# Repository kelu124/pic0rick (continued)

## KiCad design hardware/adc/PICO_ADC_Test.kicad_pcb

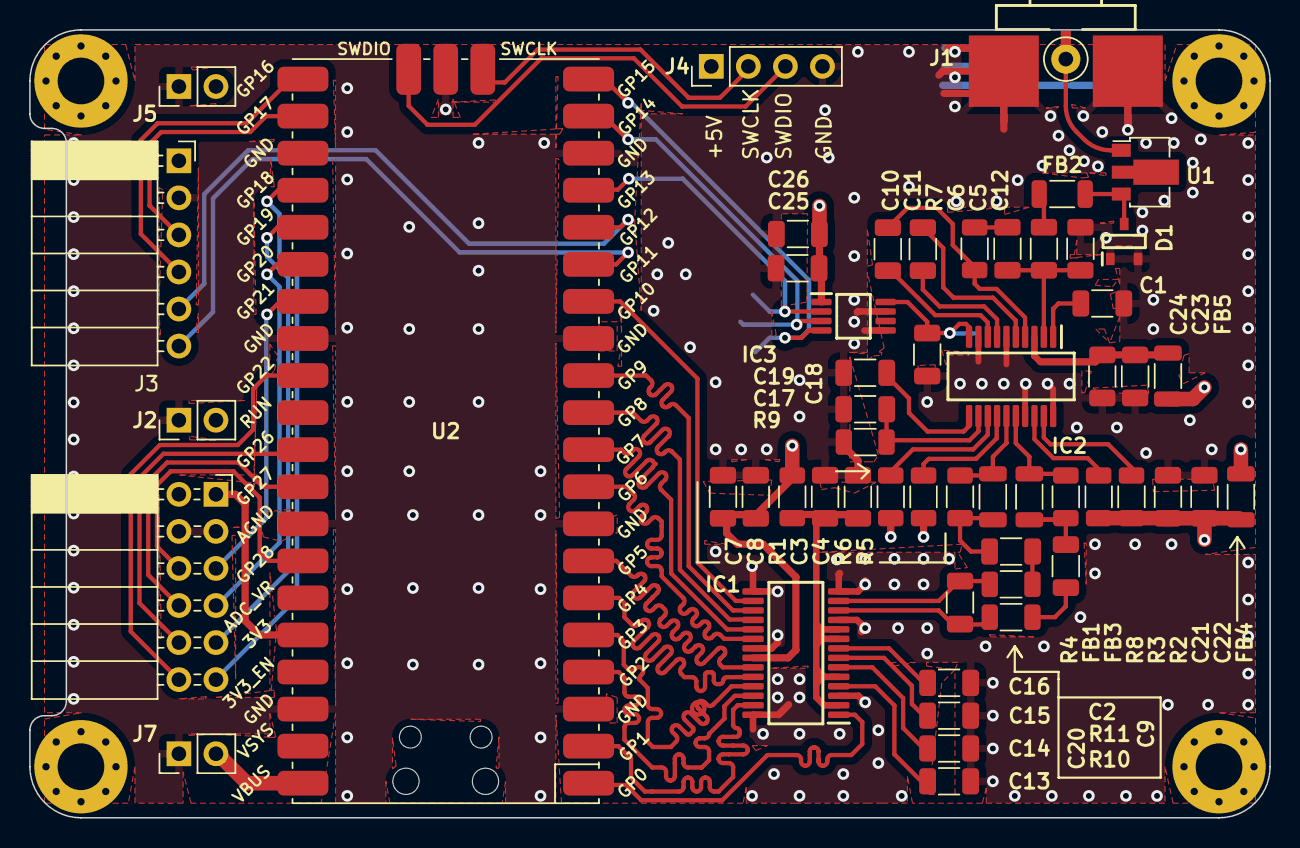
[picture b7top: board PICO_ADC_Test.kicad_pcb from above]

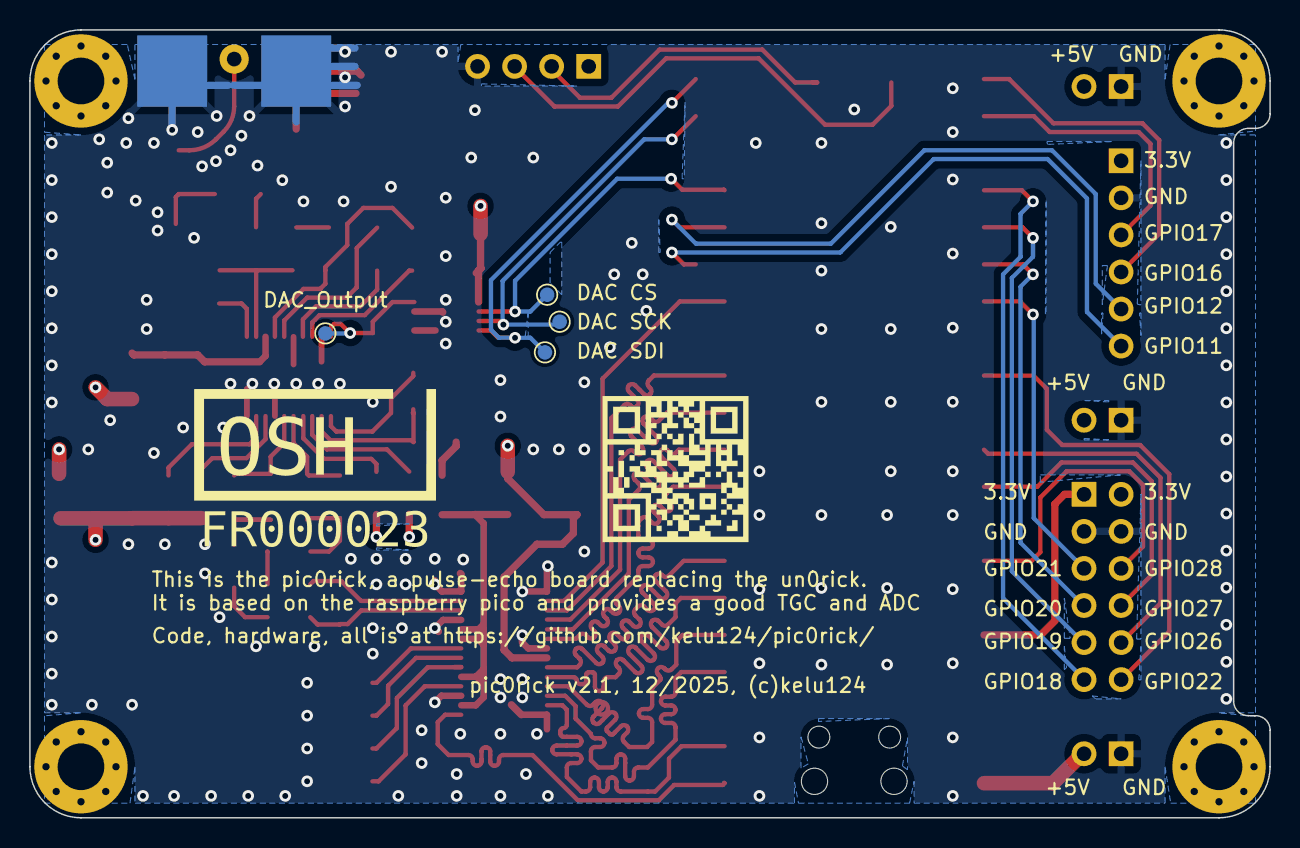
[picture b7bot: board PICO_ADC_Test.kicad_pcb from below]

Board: 4 copper layers, 85.0 x 54.0 mm, 59 parts (4 on the bottom side), 63 nets.

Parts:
C1, C2, C4, C5, C8, C9, C10, C11, C13, C14, C15, C16, C17, C19, C22, C24, C26: 100nF; C_1206_3216Metric
C3, C7: 4.7uF; C_1206_3216Metric
C6: 18nF; C_1206_3216Metric
C12: 22pF; C_1206_3216Metric
C18, C21, C23: 1nF; C_1206_3216Metric
C20: 50pF; C_1206_3216Metric
C25: 10uF; C_1206_3216Metric
D1: BAV99-7-F; SOT95P240X120-3N
FB1, FB2, FB3, FB4, FB5: ILHB1206ER750V; L_1206_3216Metric
IC1: ADC10065CIMT_NOPB; SOP65P640X120-28N
IC2: AD8331ARQZ; SOP64P600X175-20N
IC3: MCP4812-E_MS; MCP4812-EMS
J1: AMPHENOL_132357-11
J2, J5, J7: SSQ-101-02-L-Q-RA; PinHeader_1x02_P2.54mm_Vertical
J3: 61300611121; PinSocket_1x06_P2.54mm_Horizontal
J4: 61300411121; PinHeader_1x04_P2.54mm_Vertical
J6: 90122-0126; PinSocket_2x06_P2.54mm_Horizontal
R1, R10, R11: 18R; R_1206_3216Metric
R2, R3, R5, R6: 10K; R_1206_3216Metric
R4, R8: 100R; R_1206_3216Metric
R7: 280R; R_1206_3216Metric
R9: 12K; R_1206_3216Metric
TP1, TP2, TP3, TP4: TestPoint; TestPoint_Pad_D1.0mm
U1: MD0100N8-G; SOT-89-3
U2: Pico; RPi_Pico_SMD

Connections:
5VLNA: C23.1, C24.1, FB5.2, IC2.3 (VPSL)
5VVGA: C21.1, C22.1, FB4.1, R2.1, R3.1, R5.1, R6.1
+3.3V: C7.1, C8.1, C25.1, C26.1, IC1.22 (VDDIO), IC3.1 (VDD), J3.1, J6.1, J6.2, R1.1, U2.36 (3V3)
+5V: FB4.2, FB5.1, J2.2, J4.1, J5.2, J7.2, U2.40 (VBUS)
ADC_CLK: IC1.1 (CLK), U2.1 (GPIO0)
CS: IC3.2 (~CS), TP1.1, U2.17 (GPIO13)
D0: IC1.27 (D0), U2.2 (GPIO1)
D1: IC1.26 (D1), U2.4 (GPIO2)
D2: IC1.25 (D2), U2.5 (GPIO3)
D3: IC1.24 (D3), U2.6 (GPIO4)
D4: IC1.23 (D4), U2.7 (GPIO5)
D5: IC1.20 (D5), U2.9 (GPIO6)
D6: IC1.19 (D6), U2.10 (GPIO7)
D7: IC1.18 (D7), U2.11 (GPIO8)
D8: IC1.17 (D8), U2.12 (GPIO9)
D9: IC1.16 (D9), U2.14 (GPIO10)
DAC_G: C18.1, IC2.10 (GAIN), IC3.8 (VOUTA), TP4.1
GND: C1.1, C3.2, C4.2, C7.2, C8.2, C12.2, C13.2, C14.2, C15.2, C16.2, C17.2, C18.2, C19.2, C21.2, C22.2, C23.2, C24.2, C25.2, C26.2, D1.1, D1.2, IC1.3 (VSSA_1), IC1.11 (VSSA_2), IC1.14 (VSSA_3), IC1.15 (DF), IC1.21 (VSSIO), IC1.28 (STBY), IC2.6 (COML), IC2.9 (MODE), IC2.17 (COMM_1), IC2.20 (COMM_2), IC3.5 (~LDAC), IC3.7 (VSS), J1.2, J2.1, J3.2, J4.4, J5.1, J6.3, J6.4, J7.1, R9.2, U2.3 (GND), U2.8 (GND), U2.13 (GND), U2.18 (GND), U2.23 (GND), U2.28 (GND), U2.33 (AGND), U2.38 (GND), U2.42 (GND)
GPIO11: J3.6, U2.15 (GPIO11)
GPIO12: J3.5, U2.16 (GPIO12)
GPIO16: J3.4, U2.21 (GPIO16)
GPIO17: J3.3, U2.22 (GPIO17)
GPIO18: J6.11, U2.24 (GPIO18)
GPIO19: J6.9, U2.25 (GPIO19)
GPIO20: J6.7, U2.26 (GPIO20)
GPIO21: J6.5, U2.27 (GPIO21)
GPIO22: J6.12, U2.29 (GPIO22)
GPIO26: J6.10, U2.31 (GPIO26_ADC0)
GPIO27: J6.8, U2.32 (GPIO27_ADC1)
GPIO28: J6.6, U2.34 (GPIO28_ADC2)
MOSI: IC3.4 (SDI), TP3.1, U2.20 (GPIO15)
unnamed: C2.1, FB1.2, R4.2
unnamed: C5.1, FB2.2
unnamed: C6.2, R7.1
unnamed: C9.1, FB3.2, R8.2
unnamed: C3.1, C4.1, IC1.2 (VDDA_1), IC1.5 (IRS), IC1.9 (VDDA_2), IC1.10 (VDDA_3), R1.2
unnamed: C13.1, IC1.4 (VCOM)
unnamed: C20.2, IC1.13 (VIN+), R11.1
unnamed: C20.1, IC1.12 (VIN-), R10.1
unnamed: C14.1, IC1.6 (VREF)
unnamed: C16.1, IC1.8 (VREFB)
unnamed: C15.1, IC1.7 (VREFT)
unnamed: IC2.19 (ENBL), R2.2
unnamed: IC2.18 (ENBV), R3.2
unnamed: IC2.13 (HILO), R6.2
unnamed: C5.2, C6.1, C12.1, IC2.2 (INH)
unnamed: C1.2, IC2.1 (LMD)
unnamed: C10.1, IC2.4 (LON), R7.2
unnamed: C11.1, IC2.5 (LOP)
unnamed: C17.1, IC2.12 (RCLMP), R9.1
unnamed: C19.1, IC2.11 (VCM)
unnamed: C10.2, IC2.8 (VIN)
unnamed: C11.2, IC2.7 (VIP)
unnamed: IC2.14 (VPOS), R5.2
unnamed: J1.1, U1.1 (A)
unnamed: D1.3, FB2.1, U1.3 (B)
SCLK: IC3.3 (SCK), TP2.1, U2.19 (GPIO14)
SWCLK: J4.2, U2.41 (SWCLK)
SWDIO: J4.3, U2.43 (SWDIO)
TO_ADC_H: C2.2, R11.2
TO_ADC_L: C9.2, R10.2
VOH: FB1.1, IC2.15 (VOH), R4.1
VOL: FB3.1, IC2.16 (VOL), R8.1

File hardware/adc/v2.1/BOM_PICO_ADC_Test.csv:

"Reference","Value","Footprint","MPN","Manufacturer","Size","Qty"
"C1,C2,C4,C5,C8,C9,C10,C11,C13,C14,C15,C16,C17,C19,C22,C24,C26","100nF","Capacitor_SMD:C_1206_3216Metric","VJ1206Y104KXQCW1BC","","1206","17"
"C3,C7","4.7uF","Capacitor_SMD:C_1206_3216Metric","1206ZD475KAT4A","","1206","2"
"C6","18nF","Capacitor_SMD:C_1206_3216Metric","VJ1206Y183KXAAC","","1206","1"
"C12","22pF","Capacitor_SMD:C_1206_3216Metric","VJ1206A220JXQPW1BC","","1206","1"
"C18,C21,C23","1nF","Capacitor_SMD:C_1206_3216Metric","GRM31C5C3A102JWA3L","","1206","3"
"C20","50pF","Capacitor_SMD:C_1206_3216Metric","12062A500KAT2A","KYOCERA AVX","1206","1"
"C25","10uF","Capacitor_SMD:C_1206_3216Metric","KAF31GR71C106KU","KYOCERA AVX","1206","1"
"D1","BAV99-7-F","PICO_ADC_Test:SOT95P240X120-3N","BAV99-7-F","","SOT23","1"
"FB1,FB2,FB3,FB4,FB5","ILHB1206ER750V","Inductor_SMD:L_1206_3216Metric","BLM21BB750SN1D","","1206","5"
"IC1","ADC10065CIMT_NOPB","PICO_ADC_Test:SOP65P640X120-28N","ADC10065CIMT/NOPB","","","1"
"IC2","AD8331ARQZ","PICO_ADC_Test:SOP64P600X175-20N","584-AD8331ARQZ","","","1"
"IC3","MCP4812-E_MS","PICO_ADC_Test:MCP4812-EMS","579-MCP4812-E/MS","","","1"
"J1","AMPHENOL_132357-11","PICO_ADC_Test:AMPHENOL_132357-11","142-0701-801","","","1"
"J2,J5,J7","SSQ-101-02-L-Q-RA","Connector_PinHeader_2.54mm:PinHeader_1x02_P2.54mm_Vertical","SSQ-101-02-L-Q-RA","","","3"
"J3","61300611121","Connector_PinSocket_2.54mm:PinSocket_1x06_P2.54mm_Horizontal","613012243121","","","1"
"J4","61300411121","Connector_PinHeader_2.54mm:PinHeader_1x04_P2.54mm_Vertical","61300411121","","","1"
"J6","90122-0126","Connector_PinSocket_2.54mm:PinSocket_2x06_P2.54mm_Horizontal","613012243121","","","1"
"R1,R10,R11","18R","Resistor_SMD:R_1206_3216Metric","WSL1206R1800FEA","","1206","3"
"R2,R3,R5,R6","10K","Resistor_SMD:R_1206_3216Metric","1206W4F1002T5E","","1206","4"
"R4,R8","100R","Resistor_SMD:R_1206_3216Metric","560112132023","","1206","2"
"R7","280R","Resistor_SMD:R_1206_3216Metric","CR1206-FX-2800ELF","Bourns","1206","1"
"R9","12K","Resistor_SMD:R_1206_3216Metric","CR1206-FX-1202ELF","Bourns","1206","1"
"U1","MD0100N8-G","Package_TO_SOT_SMD:SOT-89-3","MD0100N8-G","","","1"
"U2","Pico","PICO_ADC_Test:RPi_Pico_SMD","Pico","","","1"

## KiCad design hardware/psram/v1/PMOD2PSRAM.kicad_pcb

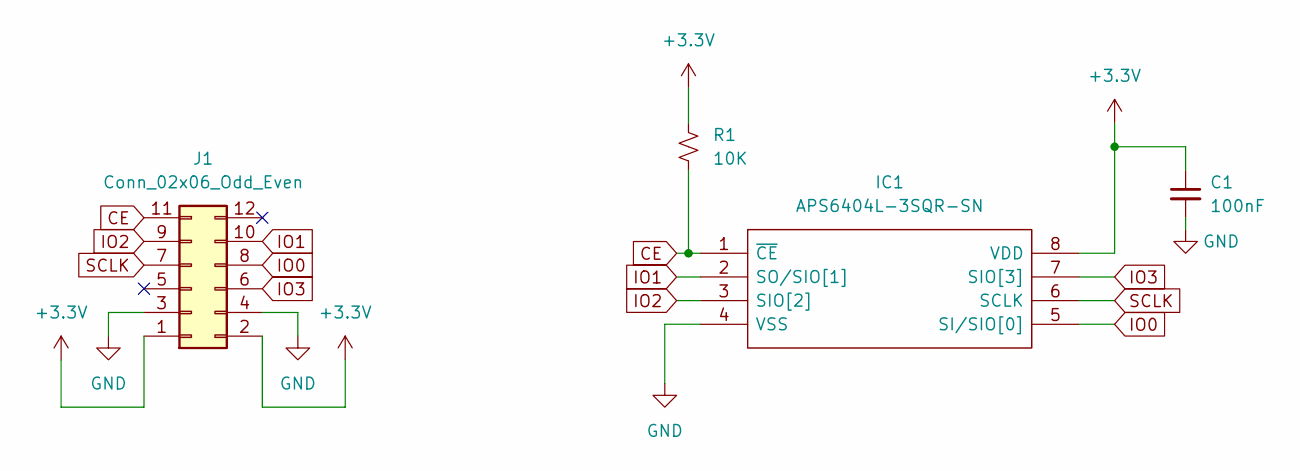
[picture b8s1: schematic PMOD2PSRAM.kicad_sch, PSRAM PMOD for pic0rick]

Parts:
C1: 100nF; C_1206_3216Metric
IC1: APS6404L-3SQR-SN; SOIC127P600X175-8N; Mouser Part Number 878-APS6404L-3SQR-SN
J1: Conn_02x06_Odd_Even; PinHeader_2x06_P2.54mm_Horizontal
R1: 10K; R_1206_3216Metric

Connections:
+3.3V: C1.1, IC1.8 (VDD), J1.1, J1.2, R1.1
CE: IC1.1 (~CE), J1.11, R1.2
GND: C1.2, IC1.4 (VSS), J1.3, J1.4
IO0: IC1.5 (SI/SIO[0]), J1.8
IO1: IC1.2 (SO/SIO[1]), J1.10
IO2: IC1.3 (SIO[2]), J1.9
IO3: IC1.7 (SIO[3]), J1.6
SCLK: IC1.6 (SCLK), J1.7

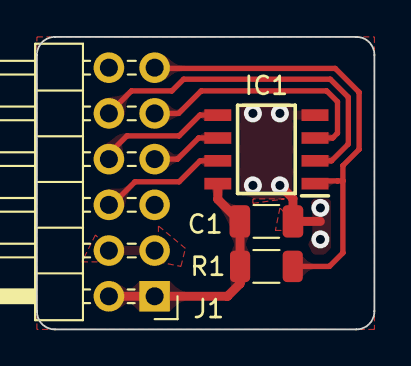
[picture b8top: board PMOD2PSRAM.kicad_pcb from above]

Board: 2 copper layers, 18.8 x 16.2 mm, 4 parts (0 on the bottom side), 8 nets.

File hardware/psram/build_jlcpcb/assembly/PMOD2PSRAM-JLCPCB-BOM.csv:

"Comment","Designator","Footprint","MPN","Manufacturer","LCSC Part #"
"100nF","C1","C_1206_3216Metric","","",""
"APS6404L-3SQR-SN","IC1","SOIC127P600X175-8N","","",""
"Conn_02x06_Odd_Even","J1","PinHeader_2x06_P2.54mm_Horizontal","","",""
"10K","R1","R_1206_3216Metric","","",""

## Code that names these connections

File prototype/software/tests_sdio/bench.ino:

/*
 * This program is a simple binary write/read benchmark.
 */
#define DISABLE_FS_H_WARNING  // Disable warning for type File not defined.
#include "SdFat.h"
#include "FreeStack.h"
#include "sdios.h"

// SD_FAT_TYPE = 0 for SdFat/File as defined in SdFatConfig.h,
// 1 for FAT16/FAT32, 2 for exFAT, 3 for FAT16/FAT32 and exFAT.
#if defined __has_include
#if __has_include(<FS.h>)
#define SD_FAT_TYPE 3  // Can't use SdFat/File
#endif  // __has_include(<FS.h>)
#endif  // defined __has_include

#ifndef SD_FAT_TYPE
#define SD_FAT_TYPE 0  // Use SdFat/File
#endif  // SD_FAT_TYPE
/*
  Change the value of SD_CS_PIN if you are using SPI and
  your hardware does not use the default value, SS.
  Common values are:
  Arduino Ethernet shield: pin 4
  Sparkfun SD shield: pin 8
  Adafruit SD shields and modules: pin 10
*/
// SDCARD_SS_PIN is defined for the built-in SD on some boards.
#ifndef SDCARD_SS_PIN
const uint8_t SD_CS_PIN = SS;
#else   // SDCARD_SS_PIN
// Assume built-in SD is used.
const uint8_t SD_CS_PIN = SDCARD_SS_PIN;
#endif  // SDCARD_SS_PIN

// Try max SPI clock for an SD. Reduce SPI_CLOCK if errors occur.
#define SPI_CLOCK SD_SCK_MHZ(50)

// Example SDIO definition for RP2040/RP2350. See the Rp2040SdioSetup example.
#if defined(ARDUINO_ADAFRUIT_METRO_RP2040) && !defined(RP_CLK_GPIO)
#define RP_CLK_GPIO 18
#define RP_CMD_GPIO 19
#define RP_DAT0_GPIO 20  // DAT1: GPIO21, DAT2: GPIO22, DAT3: GPIO23.
#endif  // defined(ARDUINO_ADAFRUIT_METRO_RP2040)



#define RP_CLK_GPIO 22
#define RP_CMD_GPIO 26
#define RP_DAT0_GPIO 16  // DAT1: GPIO19, DAT2: GPIO20, DAT3: GPIO21.
#define  SD_CONFIG SdioConfig(RP_CLK_GPIO, RP_CMD_GPIO, RP_DAT0_GPIO)

// Try to select the best SD card configuration.
#if defined(HAS_TEENSY_SDIO)
#define SD_CONFIG SdioConfig(FIFO_SDIO)
#elif defined(RP_CLK_GPIO) && defined(RP_CMD_GPIO) && defined(RP_DAT0_GPIO)
// See the Rp2040SdioSetup example for RP2040/RP2350 boards.
#define SD_CONFIG SdioConfig(RP_CLK_GPIO, RP_CMD_GPIO, RP_DAT0_GPIO)
#elif ENABLE_DEDICATED_SPI
#define SD_CONFIG SdSpiConfig(SD_CS_PIN, DEDICATED_SPI, SPI_CLOCK)
#else  // HAS_TEENSY_SDIO
#define SD_CONFIG SdSpiConfig(SD_CS_PIN, SHARED_SPI, SPI_CLOCK)
#endif  // HAS_TEENSY_SDIO

// Set PRE_ALLOCATE true to pre-allocate file clusters.
const bool PRE_ALLOCATE = false;

// Set SKIP_FIRST_LATENCY true if the first read/write to the SD can
// be avoid by writing a file header or reading the first record.
const bool SKIP_FIRST_LATENCY = true;

// Size of read/write.
const size_t BUF_SIZE = 512;

// File size in MB where MB = 1,000,000 bytes.
const uint32_t FILE_SIZE_MB = 5;

// Write pass count.
const uint8_t WRITE_COUNT = 5;

// Read pass count.
const uint8_t READ_COUNT = 5;
//==============================================================================
// End of configuration constants.
//------------------------------------------------------------------------------
// File size in bytes.
const uint32_t FILE_SIZE = 1000000UL * FILE_SIZE_MB;

// Insure 4-byte alignment.
uint32_t buf32[(BUF_SIZE + 3) / 4];
uint8_t* buf = (uint8_t*)buf32;

#if SD_FAT_TYPE == 0
SdFat sd;
File file;
#elif SD_FAT_TYPE == 1
SdFat32 sd;
File32 file;
#elif SD_FAT_TYPE == 2
SdExFat sd;
ExFile file;
#elif SD_FAT_TYPE == 3
SdFs sd;
FsFile file;
#else  // SD_FAT_TYPE
#error Invalid SD_FAT_TYPE
#endif  // SD_FAT_TYPE

// Serial output stream
ArduinoOutStream cout(Serial);
//------------------------------------------------------------------------------
// Store error strings in flash to save RAM.
#define error(s) sd.errorHalt(&Serial, F(s))
//------------------------------------------------------------------------------
void cidDmp() {
  cid_t cid;
  if (!sd.card()->readCID(&cid)) {
    error("readCID failed");
  }
  cout << F("\nManufacturer ID: ");
  cout << uppercase << showbase << hex << int(cid.mid) << dec << endl;
  cout << F("OEM ID: ") << cid.oid[0] << cid.oid[1] << endl;
  cout << F("Product: ");
  for (uint8_t i = 0; i < 5; i++) {
    cout << cid.pnm[i];
  }
  cout << F("\nRevision: ") << cid.prvN() << '.' << cid.prvM() << endl;
  cout << F("Serial number: ") << hex << cid.psn() << dec << endl;
  cout << F("Manufacturing date: ");
  cout << cid.mdtMonth() << '/' << cid.mdtYear() << endl;
  cout << endl;
}
//------------------------------------------------------------------------------
void clearSerialInput() {
  uint32_t m = micros();
  do {
    if (Serial.read() >= 0) {
      m = micros();
    }
  } while (micros() - m < 10000);
}
//------------------------------------------------------------------------------
void setup() {
  Serial.begin(9600);

  // Wait for USB Serial
  while (!Serial) {
    yield();
  }
  delay(1000);
  cout << F("\nUse a freshly formatted SD for best performance.\n");
  if (!ENABLE_DEDICATED_SPI) {
    cout << F(
        "\nSet ENABLE_DEDICATED_SPI nonzero in\n"
        "SdFatConfig.h for best SPI performance.\n");
  }
  if (!SD_HAS_CUSTOM_SPI && !USE_SPI_ARRAY_TRANSFER && isSpi(SD_CONFIG)) {
    cout << F(
          "\nSetting USE_SPI_ARRAY_TRANSFER nonzero in\n"
          "SdFatConfig.h may improve SPI performance.\n");
  }
  // use uppercase in hex and use 0X base prefix
  cout << uppercase << showbase << endl;
}
//------------------------------------------------------------------------------
void loop() {
  float s;
  uint32_t t;
  uint32_t maxLatency;
  uint32_t minLatency;
  uint32_t totalLatency;
  bool skipLatency;

  // Discard any input.
  clearSerialInput();

  // F() stores strings in flash to save RAM
  cout << F("Type any character to start\n");
  while (!Serial.available()) {
    yield();
  }
#if HAS_UNUSED_STACK
  cout << F("FreeStack: ") << FreeStack() << endl;
#endif  // HAS_UNUSED_STACK

  if (!sd.begin(SD_CONFIG)) {
    sd.initErrorHalt(&Serial);
  }
  if (sd.fatType() == FAT_TYPE_EXFAT) {
    cout << F("Type is exFAT") << endl;
  } else {
    cout << F("Type is FAT") << int(sd.fatType()) << endl;
  }

  cout << F("Card size: ") << sd.card()->sectorCount() * 512E-9;
  cout << F(" GB (GB = 1E9 bytes)") << endl;

  cidDmp();

  // open or create file - truncate existing file.
  if (!file.open("bench.dat", O_RDWR | O_CREAT | O_TRUNC)) {
    error("open failed");
  }

  // fill buf with known data
  if (BUF_SIZE > 1) {
    for (size_t i = 0; i < (BUF_SIZE - 2); i++) {
      buf[i] = 'A' + (i % 26);
    }
    buf[BUF_SIZE - 2] = '\r';
  }
  buf[BUF_SIZE - 1] = '\n';

  cout << F("FILE_SIZE_MB = ") << FILE_SIZE_MB << endl;
  cout << F("BUF_SIZE = ") << BUF_SIZE << F(" bytes\n");
  cout << F("Starting write test, please wait.") << endl << endl;

  // do write test
  uint32_t n = FILE_SIZE / BUF_SIZE;
  cout << F("write speed and latency") << endl;
  cout << F("speed,max,min,avg") << endl;
  cout << F("KB/Sec,usec,usec,usec") << endl;
  for (uint8_t nTest = 0; nTest < WRITE_COUNT; nTest++) {
    file.truncate(0);
    if (PRE_ALLOCATE) {
      if (!file.preAllocate(FILE_SIZE)) {
        error("preAllocate failed");
      }
    }
    maxLatency = 0;
    minLatency = 9999999;
    totalLatency = 0;
    skipLatency = SKIP_FIRST_LATENCY;
    t = millis();
    for (uint32_t i = 0; i < n; i++) {
      uint32_t m = micros();
      if (file.write(buf, BUF_SIZE) != BUF_SIZE) {
        error("write failed");
      }
      m = micros() - m;
      totalLatency += m;
      if (skipLatency) {
        // Wait until first write to SD, not just a copy to the cache.
        skipLatency = file.curPosition() < 512;
      } else {
        if (maxLatency < m) {
          maxLatency = m;
        }
        if (minLatency > m) {
          minLatency = m;
        }
      }
    }
    file.sync();
    t = millis() - t;
    s = file.fileSize();
    cout << s / t << ',' << maxLatency << ',' << minLatency;
    cout << ',' << totalLatency / n << endl;
  }
  cout << endl << F("Starting read test, please wait.") << endl;
  cout << endl << F("read speed and latency") << endl;
  cout << F("speed,max,min,avg") << endl;
  cout << F("KB/Sec,usec,usec,usec") << endl;

  // do read test
  for (uint8_t nTest = 0; nTest < READ_COUNT; nTest++) {
    file.rewind();
    maxLatency = 0;
    minLatency = 9999999;
    totalLatency = 0;
    skipLatency = SKIP_FIRST_LATENCY;
    t = millis();
    for (uint32_t i = 0; i < n; i++) {
      buf[BUF_SIZE - 1] = 0;
      uint32_t m = micros();
      int32_t nr = file.read(buf, BUF_SIZE);
      if (nr != BUF_SIZE) {
        error("read failed");
      }
      m = micros() - m;
      totalLatency += m;
      if (buf[BUF_SIZE - 1] != '\n') {
        error("data check error");
      }
      if (skipLatency) {
        skipLatency = false;
      } else {
        if (maxLatency < m) {
          maxLatency = m;
        }
        if (minLatency > m) {
          minLatency = m;
        }
      }
    }
    s = file.fileSize();
    t = millis() - t;
    cout << s / t << ',' << maxLatency << ',' << minLatency;
    cout << ',' << totalLatency / n << endl;
  }
  cout << endl << F("Done") << endl;
  file.close();
  sd.end();
}

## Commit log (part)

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2024-03-31 Adding software
2024-03-31 Hardware pieces
2024-03-31 Adding basic pieces
2024-03-31 Adding article
2024-04-05 Licenses
2024-04-06 Update doc
2024-04-06 Docs
2024-04-10 Update of readme
2024-04-13 Tests
2024-04-13 Tests polyglot
2024-04-22 Tests of R2R
2024-06-04 autoupdate
2024-09-30 Adding DAC2932 tests
2024-10-21 New shell approach
2024-10-21 Update of docs
2024-10-29 v2 of hardware along with silkscreen
2024-11-07 Update of the VGA driver to use actual PINs from the VGA header
2024-11-07 A couple more viz
2024-11-12 pulser+hv board together for prod
2024-11-19 updates datasheet
2024-11-28 Adding pnp files
2025-01-07 Testing rp2350 on a mfab batch item
2025-01-15 Updating code for pic0rick, including the MAX14866 code example
2025-05-04 Clear build
2025-06-01 Cleanup
2025-06-01 Cleanup v2
2025-09-11 Adding back sofware
2025-10-04 VGA extension updates, for pico1 and pico2
2025-10-04 PArallel pipeline, fast
2025-11-08 Creating 0.3 project
2025-11-08 Adding bench SDIO tests
2025-11-09 Acqs tests and SD bench
2025-11-11 Pulser update
2025-12-21 Update picO
2026-04-02 Main branch and main documentation
2026-04-02 GITINGORE
2026-04-02 pic0VGA
2026-04-02 Cleanup for VGA branch
2026-04-03 First tests of WIFI connections.. still work to do !
2026-04-03 gitign
2026-04-08 Updating script so to compile both for 2040 and rp2350
2026-04-08 Sanity check cleanup
2026-04-08 Adding Contributing.md
2026-05-16 Adding example of NDT data and data saving
2026-05-31 Example of processing
2026-06-08 docs: add Getting Started guide, fix gain label, add open questions
    - README: remove stray character, mention RP2350, add Getting Started
    section with firmware flashing, Python setup, quick-start code,
    serial command table with parameter details, and signal chain diagram
    - ndt_acquisition.py: correct gain field label from [dB] to raw DAC
    value (0-1023); fix same error in label() and calibrate() plot title;
    add gain/pon/poff/damp parameter docs to from_probe() docstring
2026-06-23 Adding documentation
